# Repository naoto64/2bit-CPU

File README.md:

# 2bit-CPU
2bit CPU using 74HC series logic IC.

## Overview
This is a 2bit CPU KiCad file. You can make a CPU using the 74HC series logic IC.

## Circuit Diagram

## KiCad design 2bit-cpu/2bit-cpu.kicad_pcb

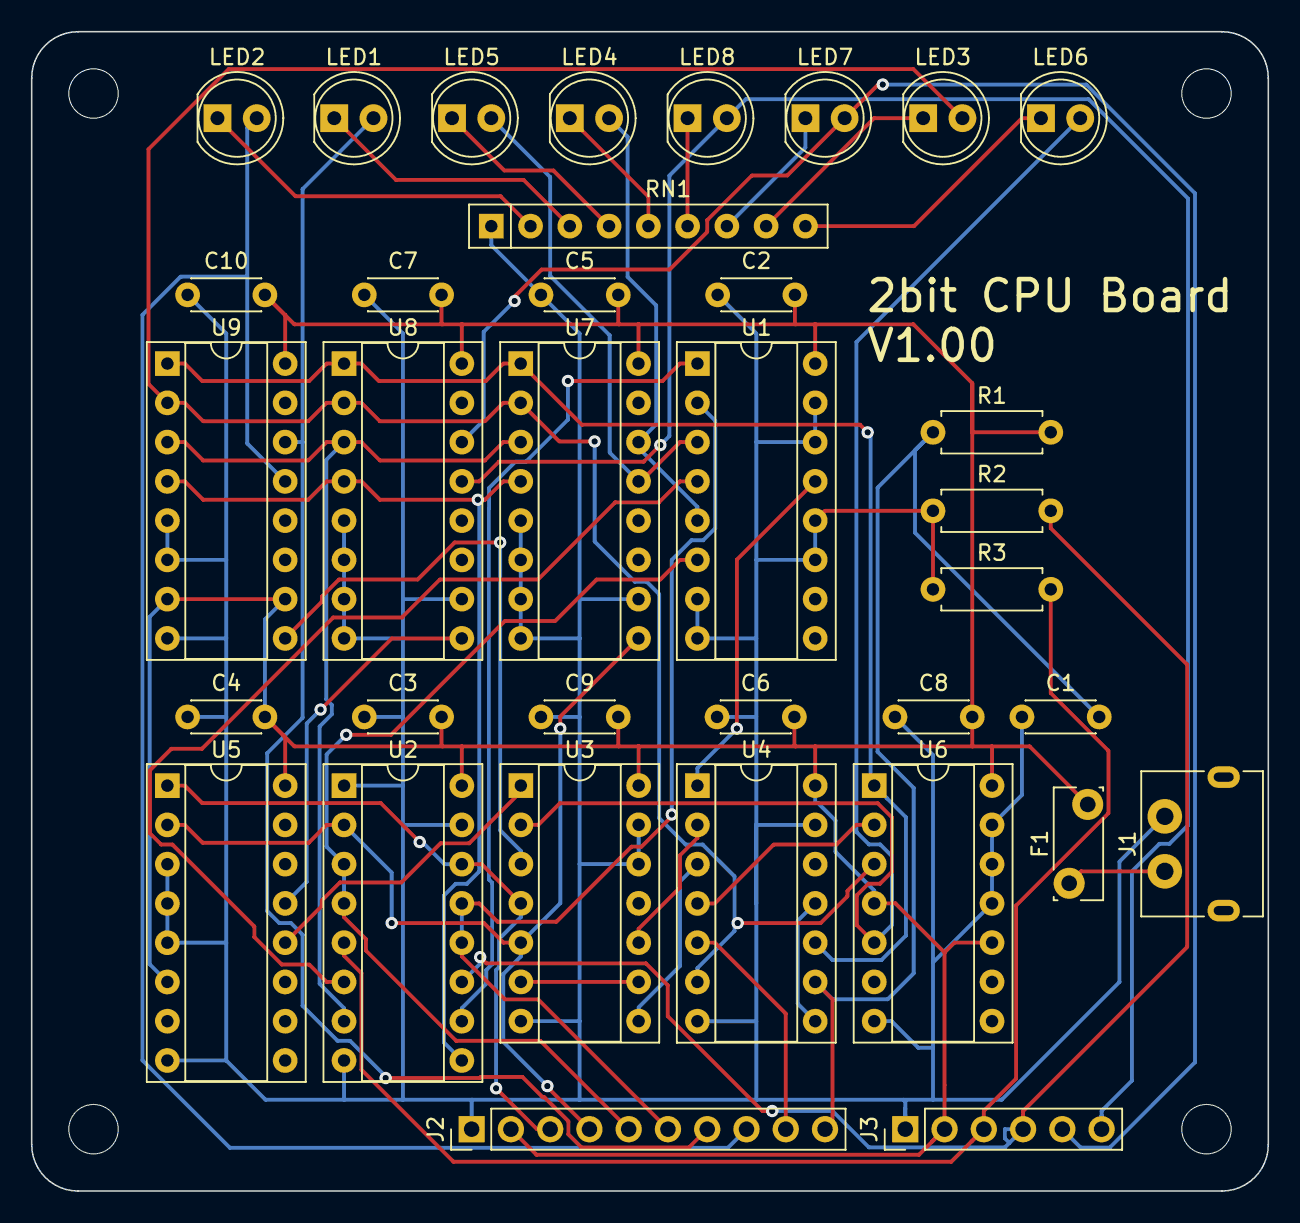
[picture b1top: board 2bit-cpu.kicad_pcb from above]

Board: 2 copper layers, 80.0 x 75.0 mm, 39 parts (0 on the bottom side), 41 nets.

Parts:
C1, C2, C3, C4, C5, C6, C7, C8, C9, C10: 0.1u; C_Disc_D4.3mm_W1.9mm_P5.00mm
F1: 100mA; Fuse_Bourns_MF-RG300
H1, H2, H3, H4: MountingHole; MountingHole_3.2mm_M3
J1: USB_Type_C; USB_C_PowerOnly
J2: Conn_01x08; PinHeader_1x10_P2.54mm_Vertical
J3: Conn_01x02; PinHeader_1x06_P2.54mm_Vertical
LED1, LED2, LED3, LED4, LED5, LED6, LED7, LED8: LED; LED_D5.0mm
R1, R2, R3: 10k; R_Axial_DIN0207_L6.3mm_D2.5mm_P7.62mm_Horizontal
RN1: 1k; R_Array_SIP9
U1: CD74HC283; DIP-16_W7.62mm_Socket
U2: 74HC153; DIP-16_W7.62mm_Socket
U3: 74HC32; DIP-14_W7.62mm_Socket
U4: 74HC14; DIP-14_W7.62mm_Socket
U5: 74HC138; DIP-16_W7.62mm_Socket
U6: 74HC74; DIP-14_W7.62mm_Socket
U7, U8, U9: CD74HC161; DIP-16_W7.62mm_Socket

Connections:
+5V: C2.2, C3.2, C4.2, C5.2, C6.2, C7.2, C8.2, C9.2, C10.2, F1.2, J2.2, J3.2, R1.2, U1.16 (VCC), U2.16 (VCC), U3.14 (VCC), U4.14 (VCC), U5.6 (E2), U5.16 (VCC), U6.4 (~S), U6.10 (~S), U6.14 (VCC), U7.16 (VCC), U8.16 (VCC), U9.7 (CEP), U9.10 (CET), U9.16 (VCC)
/Register Unit/C_Flag_In: U1.13 (S3), U4.1
/Register Unit/C_Flag_Out: LED6.2 (A), U3.2, U6.5 (Q)
/Register Unit/Clock: LED3.2 (A), U4.6, U6.3 (C), U7.2 (CP), U8.2 (CP), U9.2 (CP)
/Register Unit/Clock_In: J2.9, U4.5
/Register Unit/Cmd0: J2.3, U2.14 (A), U3.4, U5.1 (A0)
/Register Unit/Cmd1: J2.4, U2.2 (B), U3.5, U5.2 (A1), U7.9 (~PE)
/Register Unit/Data0: U2.7 (Y1), U7.3 (D0), U8.3 (D0), U9.3 (D0)
/Register Unit/Data1: U2.9 (Y2), U7.4 (D1), U8.4 (D1), U9.4 (D1)
/Register Unit/In0: J3.3, R3.2, U2.5 (1C1)
/Register Unit/In1: J3.4, R2.2, U2.11 (2C1)
/Register Unit/Out0: J3.5, LED7.2 (A), U8.14 (Q0)
/Register Unit/Out1: J3.6, LED8.2 (A), U8.13 (Q1)
/Register Unit/PC_Out0: J2.7, LED1.2 (A), U9.14 (Q0)
/Register Unit/PC_Out1: J2.8, LED2.2 (A), U9.13 (Q1)
/Register Unit/RegA_Out0: LED4.2 (A), U1.5 (A1), U7.14 (Q0)
/Register Unit/RegA_Out1: LED5.2 (A), U1.3 (A2), U7.13 (Q1)
/Register Unit/Reset: C1.2, J2.10, R1.1, U4.9
GND: C1.1, C2.1, C3.1, C4.1, C5.1, C6.1, C7.1, C8.1, C9.1, C10.1, J1.A12 (GND), J2.1, J3.1, R2.1, R3.1, RN1.1 (R1), U1.7 (C0), U1.8 (GND), U1.11 (B4), U1.12 (A4), U1.14 (A3), U1.15 (B3), U2.1 (1G), U2.8 (GND), U2.15 (2G), U3.7 (GND), U3.12, U3.13, U4.7 (GND), U4.13, U5.3 (A2), U5.4 (~E0), U5.5 (~E1), U5.8 (GND), U6.7 (GND), U6.11 (C), U6.12 (D), U6.13 (~R), U7.5 (D2), U7.6 (D3), U7.7 (CEP), U7.8 (GND), U7.10 (CET), U8.5 (D2), U8.6 (D3), U8.7 (CEP), U8.8 (GND), U8.10 (CET), U9.5 (D2), U9.6 (D3), U9.8 (GND)
unnamed: F1.1, J1.A9 (VBUS)
unnamed: J2.5, U1.6 (B1), U2.3 (1C3), U2.4 (1C2)
unnamed: J2.6, U1.2 (B2), U2.12 (2C2), U2.13 (2C3)
unnamed: LED1.1 (K), RN1.3 (R2.2)
unnamed: LED2.1 (K), RN1.2 (R1.2)
unnamed: LED3.1 (K), RN1.8 (R7.2)
unnamed: LED4.1 (K), RN1.5 (R4.2)
unnamed: LED5.1 (K), RN1.4 (R3.2)
unnamed: LED6.1 (K), RN1.9 (R8.2)
unnamed: LED7.1 (K), RN1.7 (R6.2)
unnamed: LED8.1 (K), RN1.6 (R5.2)
unnamed: U1.4 (S1), U2.6 (1C0)
unnamed: U1.1 (S2), U2.10 (2C0)
unnamed: U3.6, U3.9
unnamed: U3.8, U4.3
unnamed: U3.10, U4.2
unnamed: U4.8, U4.11
unnamed: U5.13 (~Y2), U8.9 (~PE)
unnamed: U3.1, U5.12 (~Y3)
unnamed: U4.4, U6.2 (D)
unnamed: U4.10, U6.1 (~R), U7.1 (~MR), U8.1 (~MR), U9.1 (~MR)
unnamed: U3.3, U9.9 (~PE)

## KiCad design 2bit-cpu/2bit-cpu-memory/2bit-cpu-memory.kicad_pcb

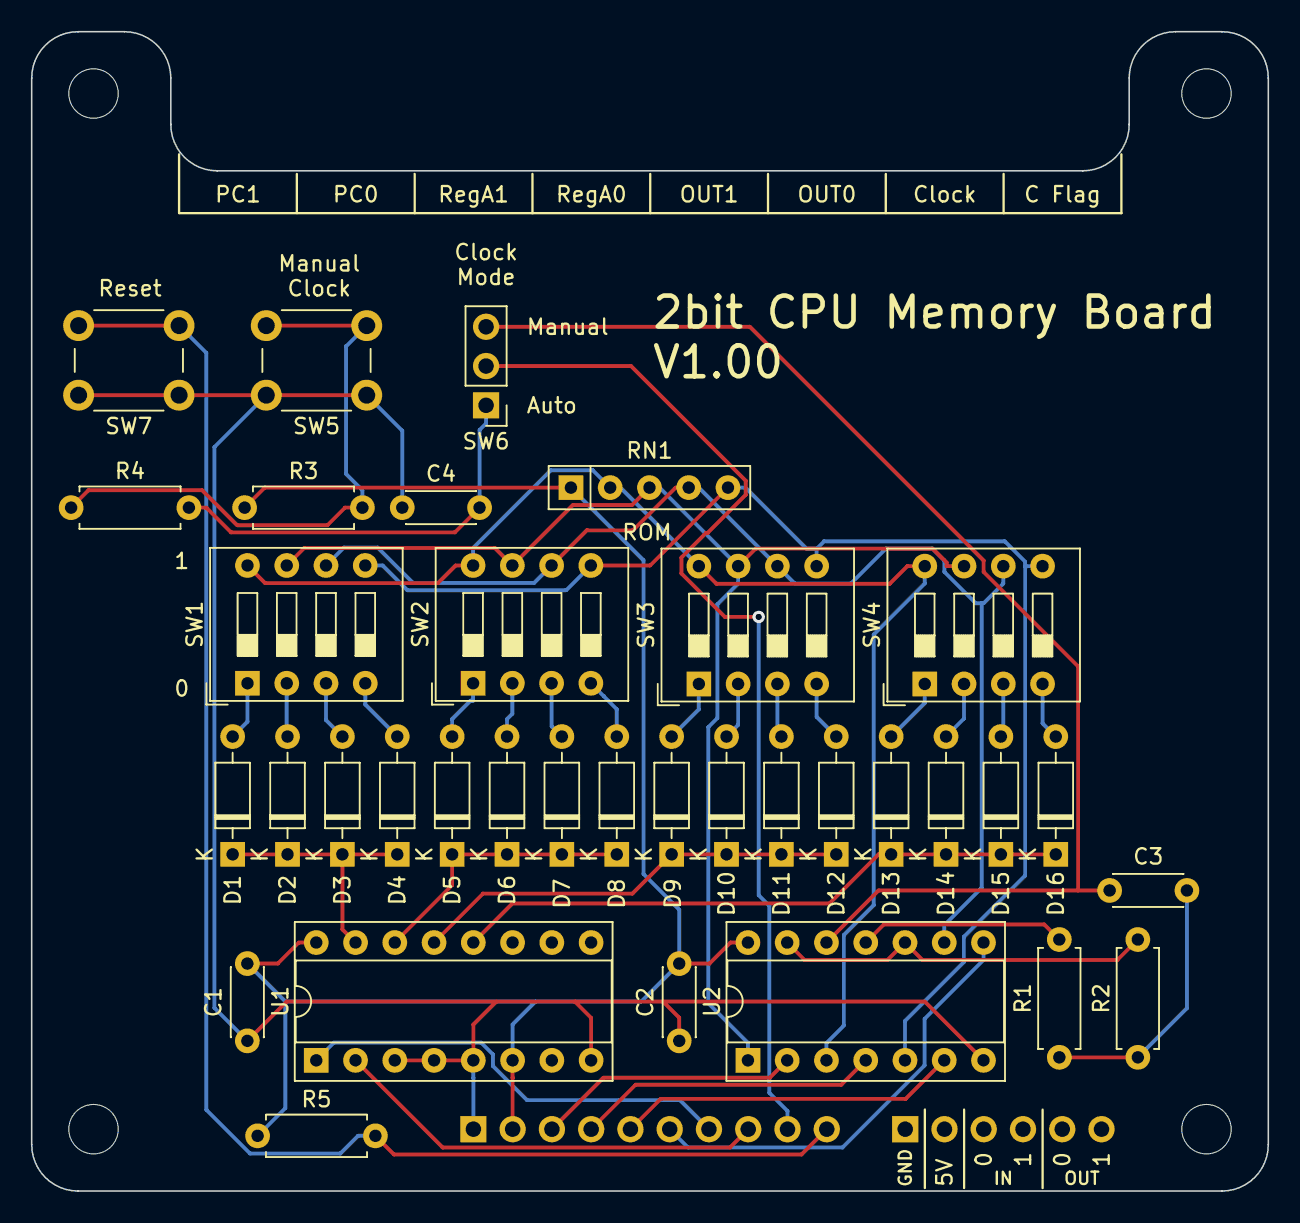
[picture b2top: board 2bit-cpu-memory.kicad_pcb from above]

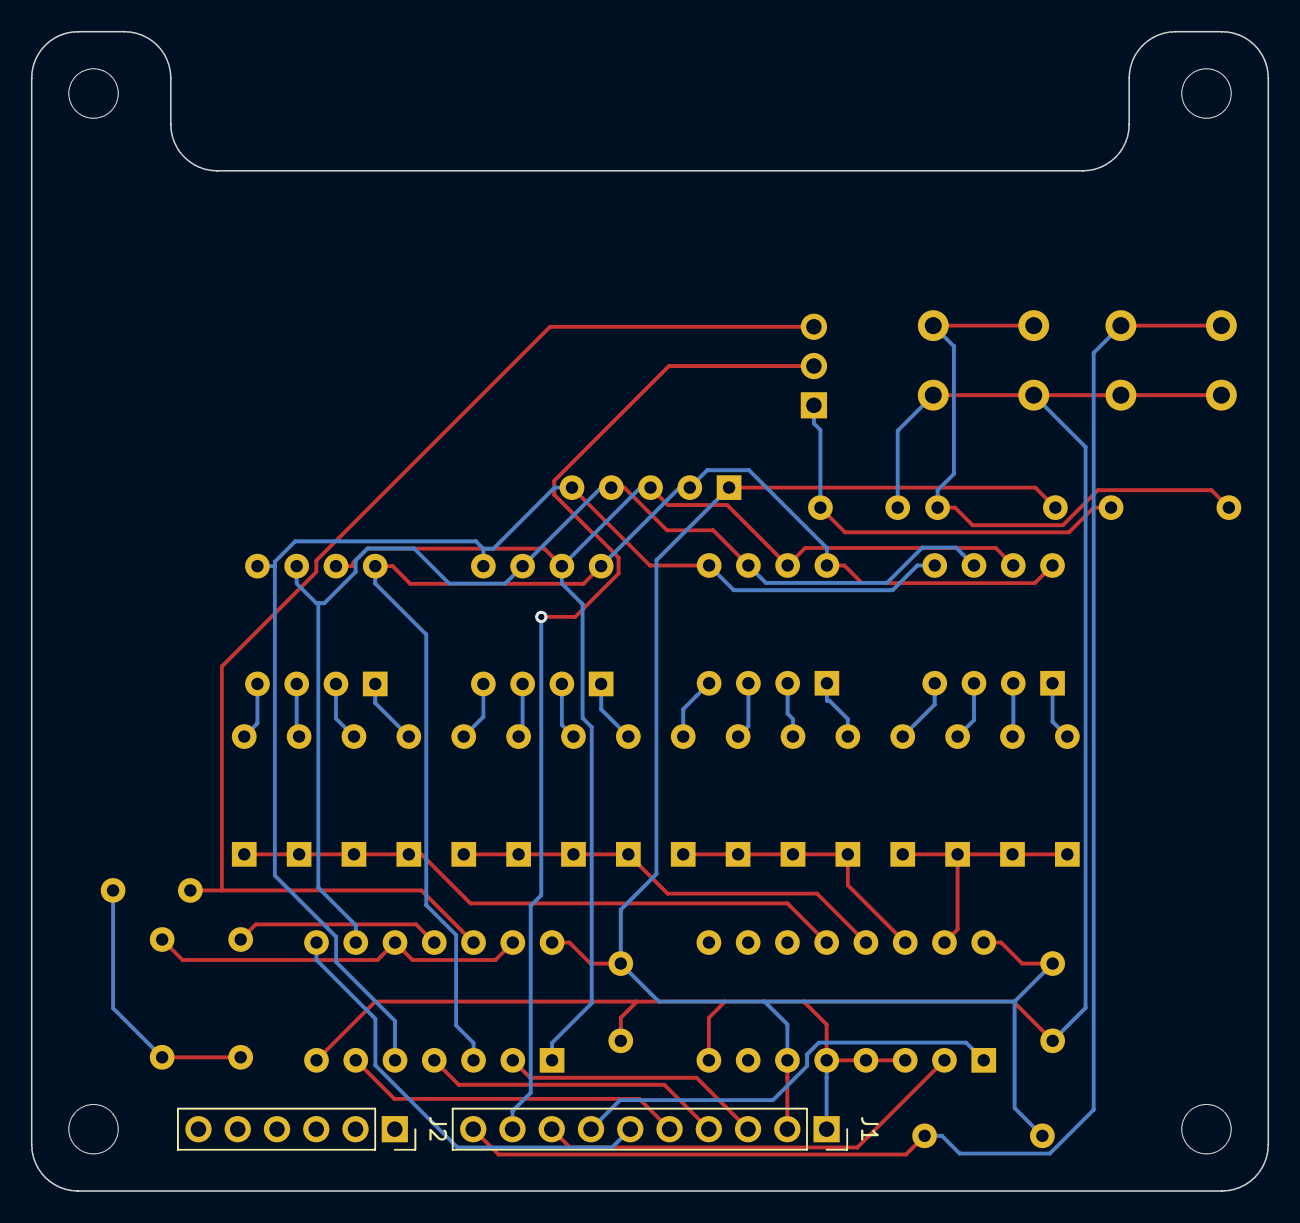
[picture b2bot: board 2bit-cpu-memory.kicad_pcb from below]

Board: 2 copper layers, 80.0 x 75.0 mm, 41 parts (2 on the bottom side), 40 nets.

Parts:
C1, C2: 0.1u; C_Disc_D4.3mm_W1.9mm_P5.00mm
C3, C4: 10u; C_Disc_D4.3mm_W1.9mm_P5.00mm
D1, D2, D3, D4, D5, D6, D7, D8, D9, D10, D11, D12, D13, D14, D15, D16: 1N4148; D_DO-35_SOD27_P7.62mm_Horizontal
H1, H2, H3, H4: MountingHole; MountingHole_3.2mm_M3
J1: Conn_01x08; PinSocket_1x10_P2.54mm_Vertical
J2: Conn_01x02; PinSocket_1x06_P2.54mm_Vertical
R1: 100k; R_Axial_DIN0207_L6.3mm_D2.5mm_P7.62mm_Horizontal
R2: 47k; R_Axial_DIN0207_L6.3mm_D2.5mm_P7.62mm_Horizontal
R3: 1k; R_Axial_DIN0207_L6.3mm_D2.5mm_P7.62mm_Horizontal
R4, R5: 10k; R_Axial_DIN0207_L6.3mm_D2.5mm_P7.62mm_Horizontal
RN1: 10k; R_Array_SIP5
SW1, SW2, SW3, SW4: SW_DIP_x04; SW_DIP_SPSTx04_Slide_9.78x12.34mm_W7.62mm_P2.54mm
SW5, SW7: SW_Push; SW_PUSH_6mm
SW6: SW_SPDT; PinHeader_1x03_P2.54mm_Vertical
U1: 74HC138; DIP-16_W7.62mm_Socket
U2: 74HC14; DIP-14_W7.62mm_Socket

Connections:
+5V: C1.2, C2.2, J1.2, R3.1, R5.1, RN1.1 (common), U1.6 (E2), U1.16 (VCC), U2.14 (VCC)
Clock: J1.9, SW6.2 (B)
GND: C1.1, C2.1, C4.1, J1.1, SW5.1, SW7.1, U1.3 (A2), U1.4 (~E0), U1.5 (~E1), U1.8 (GND), U2.7 (GND)
unnamed: C3.2, R1.1, R2.1
unnamed: D1.2 (A), SW1.1
unnamed: D1.1 (K), D2.1 (K), D3.1 (K), D4.1 (K), U1.15 (~Y0)
unnamed: D2.2 (A), SW1.2
unnamed: D3.2 (A), SW1.3
unnamed: D4.2 (A), SW1.4
unnamed: D5.2 (A), SW2.1
unnamed: D5.1 (K), D6.1 (K), D7.1 (K), D8.1 (K), U1.14 (~Y1)
unnamed: D6.2 (A), SW2.2
unnamed: D7.2 (A), SW2.3
unnamed: D8.2 (A), SW2.4
unnamed: D9.2 (A), SW3.1
unnamed: D10.2 (A), SW3.2
unnamed: D9.1 (K), D10.1 (K), D11.1 (K), D12.1 (K), U1.13 (~Y2)
unnamed: D11.2 (A), SW3.3
unnamed: D12.2 (A), SW3.4
unnamed: D13.2 (A), SW4.1
unnamed: D13.1 (K), D14.1 (K), D15.1 (K), D16.1 (K), U1.12 (~Y3)
unnamed: D14.2 (A), SW4.2
unnamed: D15.2 (A), SW4.3
unnamed: D16.2 (A), SW4.4
unnamed: J1.3, U2.2
unnamed: J1.4, U2.4
unnamed: J1.5, U2.6
unnamed: J1.6, U2.8
unnamed: J1.7, U1.1 (A0)
unnamed: J1.8, U1.2 (A1)
unnamed: R1.2, U2.11
unnamed: R2.2, U2.10, U2.13
unnamed: R3.2, R4.1, SW5.2
unnamed: RN1.2 (R1), SW1.8, SW2.8, SW3.8, SW4.8, U2.3
unnamed: RN1.3 (R2), SW1.7, SW2.7, SW3.7, SW4.7, U2.1
unnamed: RN1.4 (R3), SW1.6, SW2.6, SW3.6, SW4.6, U2.9
unnamed: RN1.5 (R4), SW1.5, SW2.5, SW3.5, SW4.5, U2.5
unnamed: C4.2, R4.2, SW6.1 (A)
unnamed: C3.1, SW6.3 (C), U2.12
Reset: J1.10, R5.2, SW7.2

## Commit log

2024-09-09 Rename schematic1.jpg to schematic01.jpg
2024-09-09 Rename schematic2.jpg to schematic02.jpg
2024-09-09 Rename schematic3.jpg to schematic03.jpg
2024-09-18 Rename implementation-diagram01.jpg to implementation-example01.jpg
2024-09-18 Rename implementation-diagram02.jpg to implementation-example02.jpg
2024-09-19 Rename manual.pdf to manual_8202_20240919.pdf
